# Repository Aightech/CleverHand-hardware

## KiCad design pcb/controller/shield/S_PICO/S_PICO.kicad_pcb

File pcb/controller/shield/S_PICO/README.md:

# pico shield
This shield is made to connect a pico board from seeed studio to the CleverHand bus and control the hmi modules.

## Electrical Schematic

## PCB Layout
|top view|side view|
|---|---|
|  |  |

## 3D Model
[S_PICO_3D](plots/S_PICO_pcb.stl)

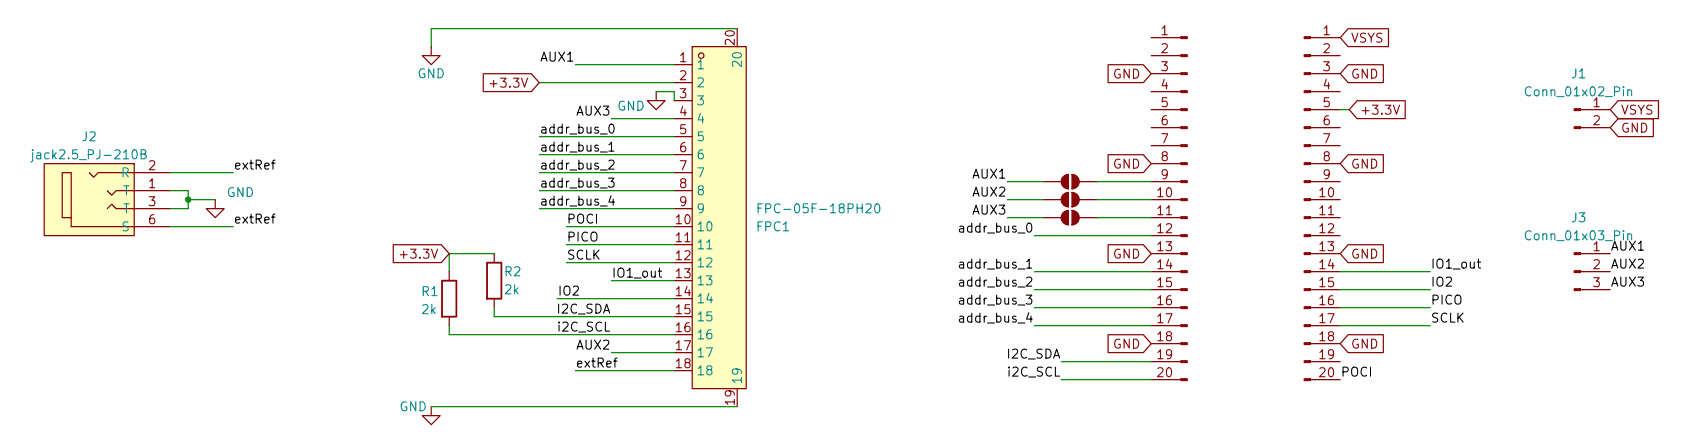
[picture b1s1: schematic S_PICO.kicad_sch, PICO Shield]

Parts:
FPC1: FPC-05F-18PH20; FPC-SMD_18P-P0.50_X05C2018TZ; LCSC Part C397324
J1: Conn_01x02_Pin; PinHeader_1x02_P1.27mm_Vertical
J2: jack2.5_PJ-210B; Jack_Socket_PJ-210B
J3: Conn_01x03_Pin; PinSocket_1x03_P1.27mm_Vertical
J4, J5: Conn_01x20_Male; PinHeader_1x20_P2.54mm_Vertical
JP2, JP3, JP4: SolderJumper_2_Open; SolderJumper-2_P1.3mm_Open_TrianglePad1.0x1.5mm
R1, R2: 2k; R_0402_1005Metric_Pad0.72x0.64mm_HandSolder; LCSC Part C4109

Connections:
+3.3V: FPC1.2, J5.5, R1.1, R2.1
/AUX1: FPC1.1, J3.1, JP2.1 (A)
/AUX2: FPC1.17, J3.2, JP3.1 (A)
/AUX3: FPC1.4, J3.3, JP4.1 (A)
/I2C_SDA: FPC1.15, J4.19, R2.2
/IO1_out: FPC1.13, J5.14
/IO2: FPC1.14, J5.15
/PICO: FPC1.11, J5.16
/POCI: FPC1.10, J5.20
/SCLK: FPC1.12, J5.17
/addr_bus_0: FPC1.5, J4.12
/addr_bus_1: FPC1.6, J4.14
/addr_bus_2: FPC1.7, J4.15
/addr_bus_3: FPC1.8, J4.16
/addr_bus_4: FPC1.9, J4.17
/extRef: FPC1.18, J2.2 (R), J2.6 (S)
/i2C_SCL: FPC1.16, J4.20, R1.2
GND: FPC1.3, FPC1.19, FPC1.20, J1.2, J2.1 (T), J2.3 (T), J4.3, J4.8, J4.13, J4.18, J5.3, J5.8, J5.13, J5.18
unnamed: J4.9, JP2.2 (B)
unnamed: J4.10, JP3.2 (B)
unnamed: J4.11, JP4.2 (B)
VSYS: J1.1, J5.1

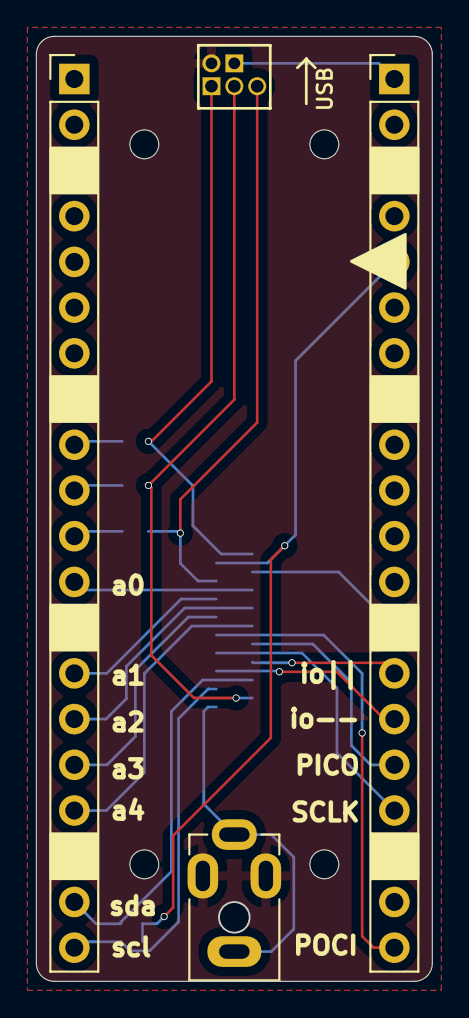
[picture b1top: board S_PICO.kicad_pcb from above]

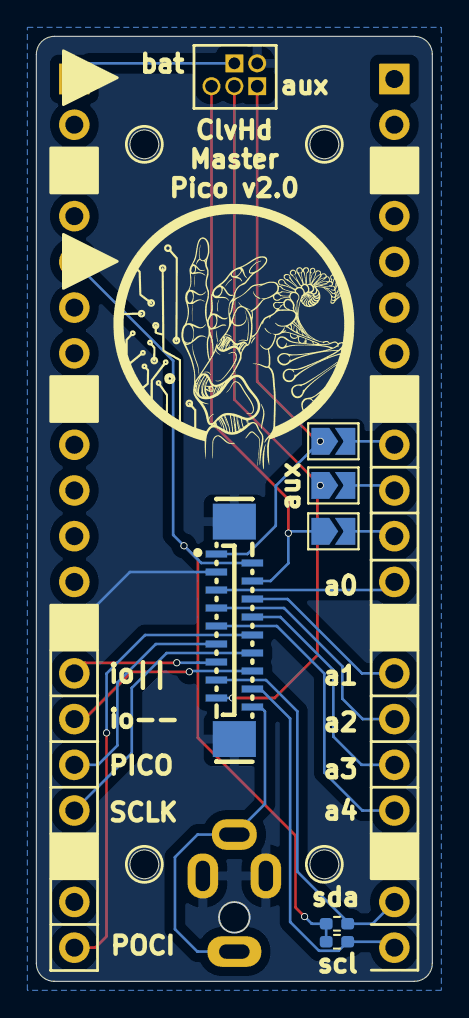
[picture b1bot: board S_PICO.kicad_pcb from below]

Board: 4 copper layers, 22.0 x 52.5 mm, 11 parts (6 on the bottom side), 22 nets.

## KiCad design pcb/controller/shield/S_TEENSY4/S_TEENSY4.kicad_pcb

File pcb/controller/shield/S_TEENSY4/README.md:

# XIAO shield
This shield is made to connect a teensy 4 board to the CleverHand bus and control the hmi modules.

## Electrical Schematic

## PCB Layout
|top view|side view|
|---|---|
|  |  |

## 3D Model
[S_TEENSY4_3D](plots/S_TEENSY4_pcb.stl)

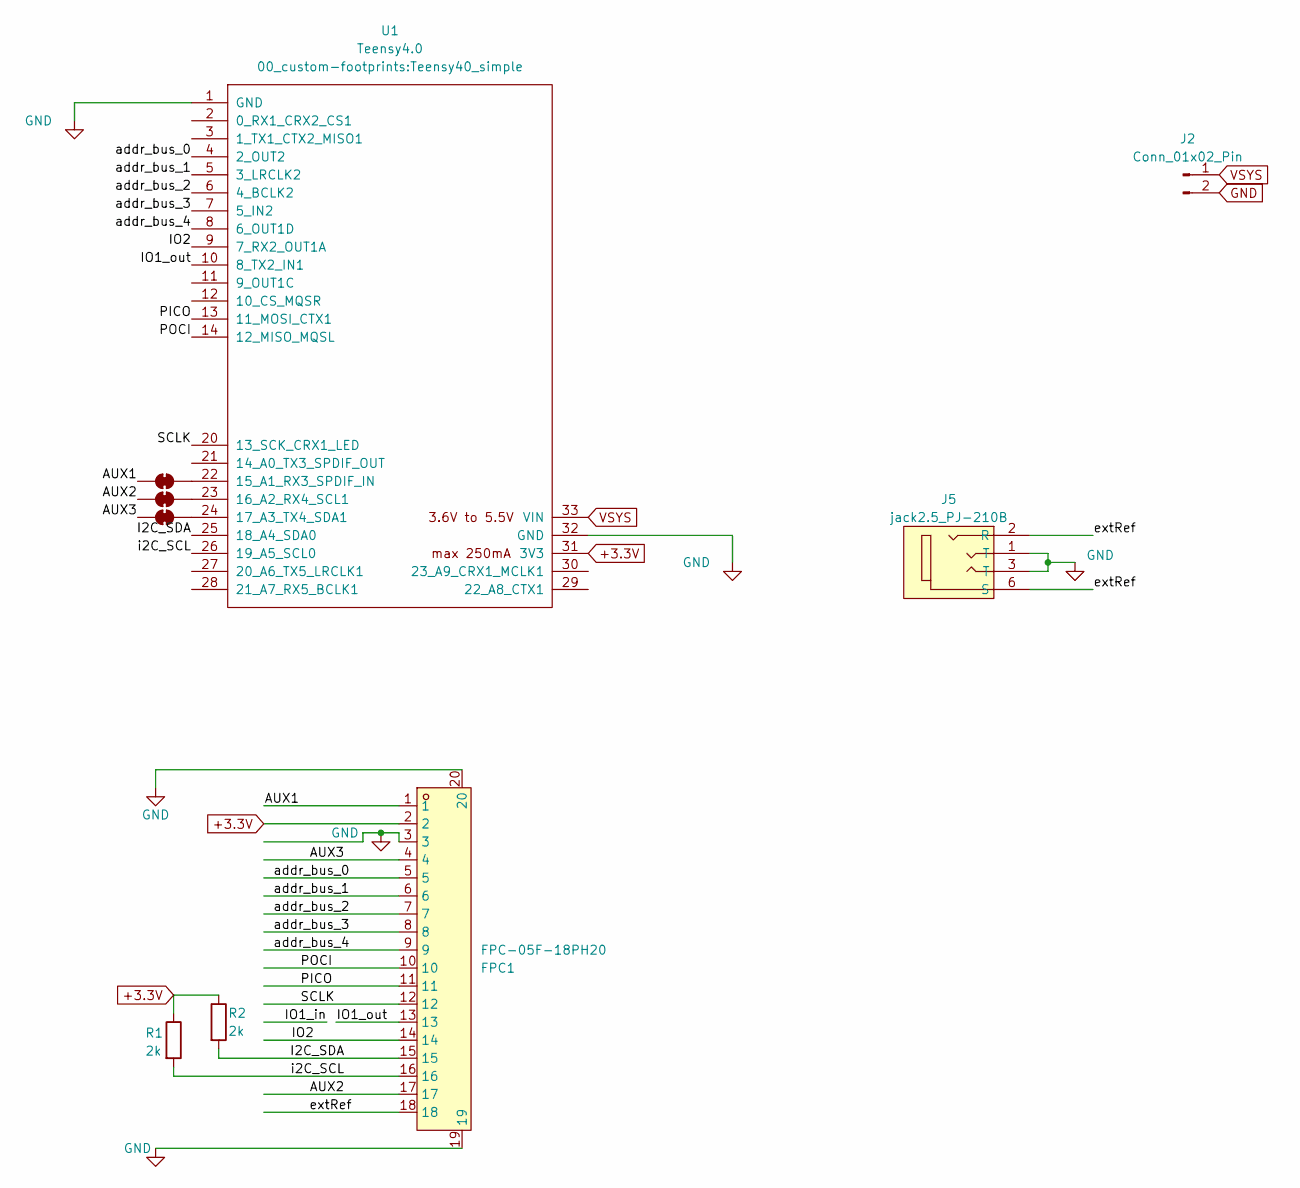
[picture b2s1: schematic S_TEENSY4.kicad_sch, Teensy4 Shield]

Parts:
FPC1: FPC-05F-18PH20; FPC-SMD_18P-P0.50_X05C2018TZ; LCSC Part C397324
J2: Conn_01x02_Pin; PinHeader_1x02_P1.27mm_Vertical
J5: jack2.5_PJ-210B; Jack_Socket_PJ-210B
JP1, JP2, JP3: SolderJumper_2_Bridged; SolderJumper-2_P1.3mm_Bridged_RoundedPad1.0x1.5mm
R1, R2: 2k; R_0402_1005Metric_Pad0.72x0.64mm_HandSolder; LCSC Part C4109
U1: Teensy4.0; Teensy40_simple

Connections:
+3.3V: FPC1.2, R1.1, R2.1, U1.31 (3V3)
/AUX1: FPC1.1, JP1.1 (A)
/AUX2: FPC1.17, JP2.1 (A)
/AUX3: FPC1.4, JP3.1 (A)
/I2C_SDA: FPC1.15, R2.2, U1.25 (18_A4_SDA0)
/IO1_out: FPC1.13, U1.10 (8_TX2_IN1)
/IO2: FPC1.14, U1.9 (7_RX2_OUT1A)
/PICO: FPC1.11, U1.13 (11_MOSI_CTX1)
/POCI: FPC1.10, U1.14 (12_MISO_MQSL)
/SCLK: FPC1.12, U1.20 (13_SCK_CRX1_LED)
/addr_bus_0: FPC1.5, U1.4 (2_OUT2)
/addr_bus_1: FPC1.6, U1.5 (3_LRCLK2)
/addr_bus_2: FPC1.7, U1.6 (4_BCLK2)
/addr_bus_3: FPC1.8, U1.7 (5_IN2)
/addr_bus_4: FPC1.9, U1.8 (6_OUT1D)
/extRef: FPC1.18, J5.2 (R), J5.6 (S)
/i2C_SCL: FPC1.16, R1.2, U1.26 (19_A5_SCL0)
GND: FPC1.3, FPC1.19, FPC1.20, J2.2, J5.1 (T), J5.3 (T), U1.1 (GND), U1.32 (GND)
unnamed: JP1.2 (B), U1.22 (15_A1_RX3_SPDIF_IN)
unnamed: JP2.2 (B), U1.23 (16_A2_RX4_SCL1)
unnamed: JP3.2 (B), U1.24 (17_A3_TX4_SDA1)
VSYS: J2.1, U1.33 (VIN)

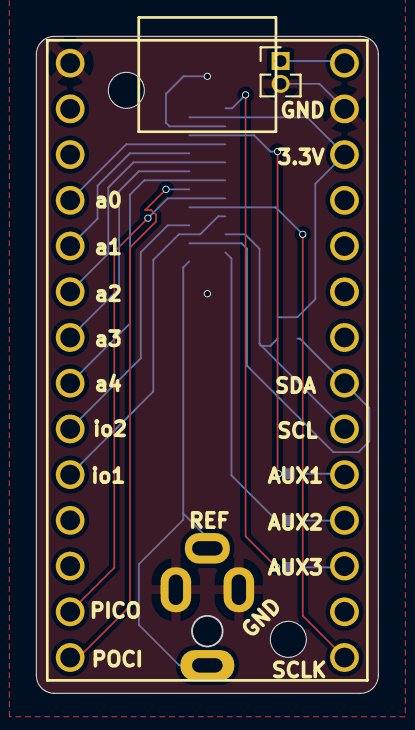
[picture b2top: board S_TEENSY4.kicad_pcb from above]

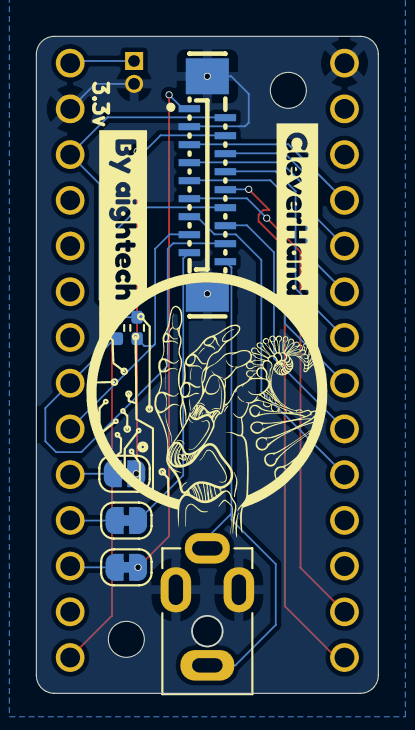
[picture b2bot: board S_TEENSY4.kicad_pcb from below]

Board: 4 copper layers, 19.0 x 36.5 mm, 11 parts (9 on the bottom side), 22 nets.

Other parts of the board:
kibuzzard-6611AB09: G***; kibuzzard-6611AB09
kibuzzard-6611ABB8: G***; kibuzzard-6611ABB8

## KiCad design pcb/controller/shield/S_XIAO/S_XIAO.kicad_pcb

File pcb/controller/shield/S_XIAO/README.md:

# XIAO shield
This shield is made to connect a XIAO board from seeed studio to the CleverHand bus and control the hmi modules.

## Electrical Schematic

## PCB Layout
|top view|side view|
|---|---|
|  |  |

## 3D Model
[S_XIAO_3D](plots/S_XIAO_pcb.stl)

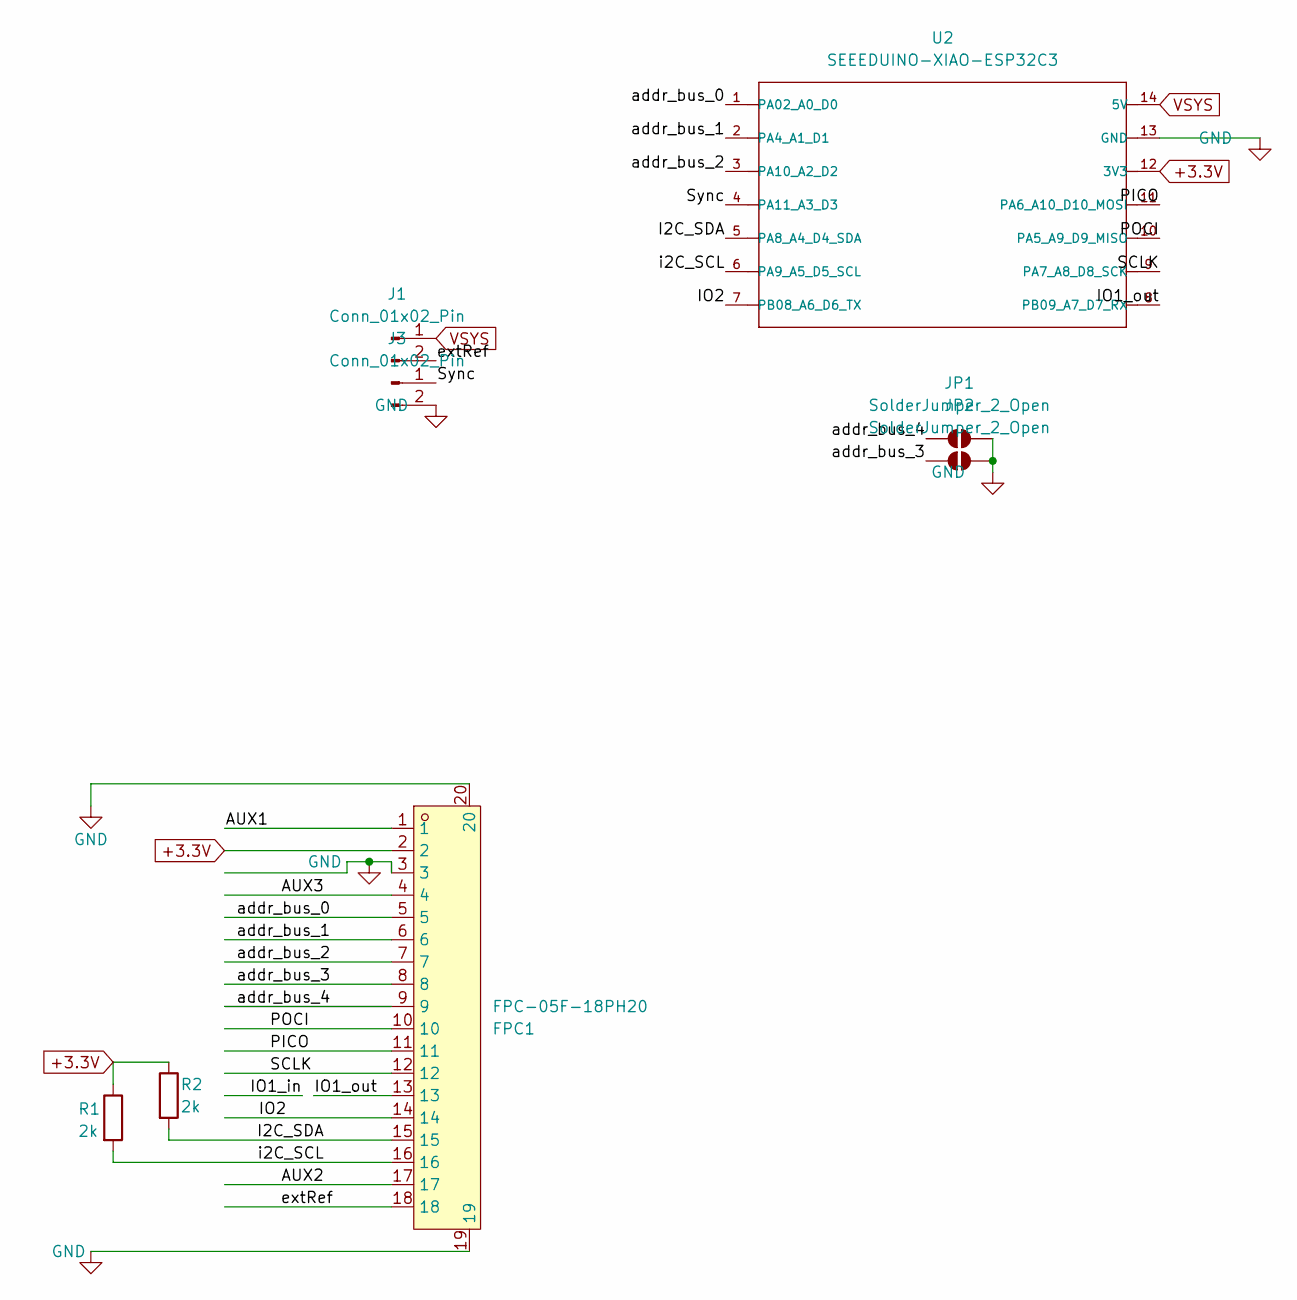
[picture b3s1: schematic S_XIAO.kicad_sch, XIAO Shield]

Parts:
FPC1: FPC-05F-18PH20; FPC-SMD_18P-P0.50_FPC-05F-18PH20; LCSC Part C397324
J1, J3: Conn_01x02_Pin; PinHeader_1x02_P2.54mm_Vertical
JP1, JP2: SolderJumper_2_Open; SolderJumper-2_P1.3mm_Open_Pad1.0x1.5mm
R1, R2: 2k; R_0402_1005Metric_Pad0.72x0.64mm_HandSolder; LCSC Part C4109
U2: SEEEDUINO-XIAO-ESP32C3; xiaoSeeedStudio_MODULE14P-DIP

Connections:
+3.3V: FPC1.2, R1.1, R2.1, U2.12 (3V3)
/AUX1: FPC1.1
/AUX2: FPC1.17
/AUX3: FPC1.4
/I2C_SDA: FPC1.15, R2.2, U2.5 (PA8_A4_D4_SDA)
/IO1_out: FPC1.13, U2.8 (PB09_A7_D7_RX)
/IO2: FPC1.14, U2.7 (PB08_A6_D6_TX)
/PICO: FPC1.11, U2.11 (PA6_A10_D10_MOSI)
/POCI: FPC1.10, U2.10 (PA5_A9_D9_MISO)
/SCLK: FPC1.12, U2.9 (PA7_A8_D8_SCK)
/Sync: J3.1, U2.4 (PA11_A3_D3)
/addr_bus_0: FPC1.5, U2.1 (PA02_A0_D0)
/addr_bus_1: FPC1.6, U2.2 (PA4_A1_D1)
/addr_bus_2: FPC1.7, U2.3 (PA10_A2_D2)
/addr_bus_3: FPC1.8, JP2.1 (A)
/addr_bus_4: FPC1.9, JP1.1 (A)
/extRef: FPC1.18, J1.2
/i2C_SCL: FPC1.16, R1.2, U2.6 (PA9_A5_D5_SCL)
GND: FPC1.3, FPC1.19, FPC1.20, J3.2, JP1.2 (B), JP2.2 (B), U2.13 (GND)
VSYS: J1.1, U2.14 (5V)

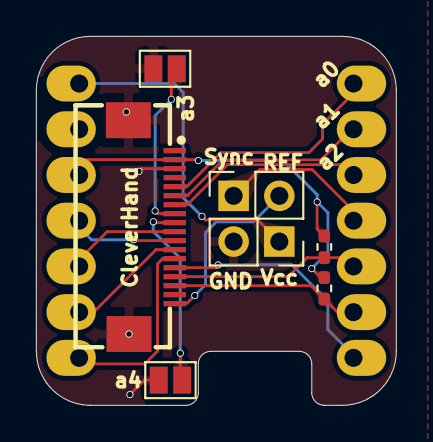
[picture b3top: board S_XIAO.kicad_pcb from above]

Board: 4 copper layers, 20.0 x 20.5 mm, 8 parts (1 on the bottom side), 17 nets.

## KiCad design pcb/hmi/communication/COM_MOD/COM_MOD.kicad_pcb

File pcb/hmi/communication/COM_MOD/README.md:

# Communication Module
This module is responsible for handling the communication between the different modules of the controller node.

The communication bus is composed of :
- Power supply (3.3V) and ground
- SPI bus (POCI, PICO, SCK)
- I2C bus (SDA, SCL)
- Address bus (A0, A1, A2, A3, A4)
- External reference voltage (AREF)

When the module is connected to the bus, it is assigned an address by the controller node. This address is used to identify the module on the bus.
The communication module will activate the chip select line of the associated sensor module when the address bus matches its address.
Additionally, each module has a unique identifier that is used to identify the module on the I2C bus.

## Electrical Schematic

## PCB Layout
|top view|side view|
|---|---|
 |  |  |

## 3D Model
[COM_MOD_3D](plots/COM_MOD_pcb.stl)

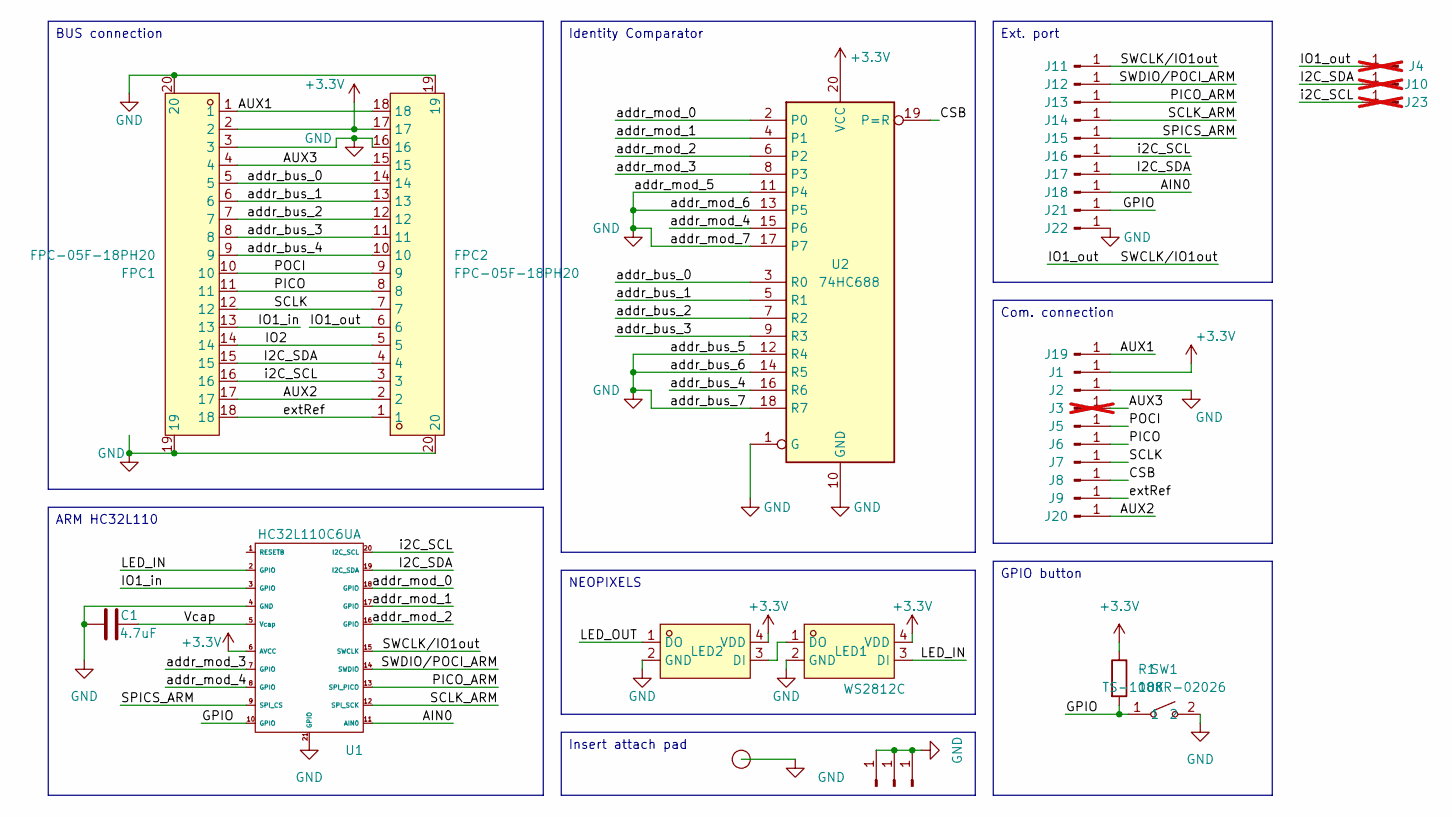
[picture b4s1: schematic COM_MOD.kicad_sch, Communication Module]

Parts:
C1: 4.7uF; C_0402_1005Metric; LCSC C23733
FPC1, FPC2: FPC-05F-18PH20; FPC-SMD_18P-P0.50_FPC-05F-18PH20; LCSC Part C2856802
I1: smd_insert; insert_1.2mm
J1, J2, J5, J6, J7, J8, J9, J11, J12, J13, J14, J15, J16, J17, J18, J19, J20, J21, J22: Conn_01x01_Pin; PinHeader_1x01_P1.27mm_Vertical
J3, J4, J10, J23: Conn_01x01_Pin; PinHeader_1x01_P1.27mm_Vertical; not fitted
J24, J25, J26: Conn_01x01_Pin; PinSocket_1x01_P2.54mm_Vertical
LED1, LED2: WS2812C; LED-SMD_4P-L2.0-W2.0-TL_WS2812B-2020; LCSC Part C2976072
R1: 10K; R_0402_1005Metric; LCSC C25744
SW1: TS-1088R-02026; SW-SMD_L3.9-W3.0-P4.45; LCSC Part C455280
U1: HC32L110C6UA; QFN-20-1EP_3x3mm_P0.4mm_EP1.4x1.4mm; LCSC C493490
U2: 74HC688; TSSOP-20_W4.4mm; LCSC C132045

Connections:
+3.3V: FPC1.2, FPC2.17, J1.1, LED1.4 (VDD), LED2.4 (VDD), R1.1, U1.6 (AVCC), U2.20 (VCC)
/AIN0: J18.1, U1.11 (AIN0)
/AUX1: FPC1.1, FPC2.18, J19.1
/AUX2: FPC1.17, FPC2.2, J20.1
/AUX3: FPC1.4, FPC2.15, J3.1
/CSB: J8.1, U2.19 (P=R)
/GPIO: J21.1, R1.2, SW1.1, U1.10 (GPIO)
/I2C_SDA: FPC1.15, FPC2.4, J10.1, J17.1, U1.19 (I2C_SDA)
/IO1_in: FPC1.13, U1.3 (GPIO)
/IO1_out: FPC2.6, J4.1, J11.1, U1.15 (SWCLK)
/IO2: FPC1.14, FPC2.5
/LED_IN: LED1.3 (DI), U1.2 (GPIO)
/LED_OUT: LED2.1 (DO)
/PICO: FPC1.11, FPC2.8, J6.1
/PICO_ARM: J13.1, U1.13 (SPI_PICO)
/POCI: FPC1.10, FPC2.9, J5.1
/SCLK: FPC1.12, FPC2.7, J7.1
/SCLK_ARM: J14.1, U1.12 (SPI_SCK)
/SPICS_ARM: J15.1, U1.9 (SPI_CS)
/SWDIO/POCI_ARM: J12.1, U1.14 (SWDIO)
/Vcap: C1.2, U1.5 (Vcap)
/addr_bus_0: FPC1.5, FPC2.14, U2.3 (R0)
/addr_bus_1: FPC1.6, FPC2.13, U2.5 (R1)
/addr_bus_2: FPC1.7, FPC2.12, U2.7 (R2)
/addr_bus_3: FPC1.8, FPC2.11, U2.9 (R3)
/addr_bus_4: FPC1.9, FPC2.10, U2.16 (R6)
/addr_mod_0: U1.18 (GPIO), U2.2 (P0)
/addr_mod_1: U1.17 (GPIO), U2.4 (P1)
/addr_mod_2: U1.16 (GPIO), U2.6 (P2)
/addr_mod_3: U1.7 (GPIO), U2.8 (P3)
/addr_mod_4: U1.8 (GPIO), U2.15 (P6)
/extRef: FPC1.18, FPC2.1, J9.1
/i2C_SCL: FPC1.16, FPC2.3, J16.1, J23.1, U1.20 (I2C_SCL)
GND: C1.1, FPC1.3, FPC1.19, FPC1.20, FPC2.16, FPC2.19, FPC2.20, I1.1 (conn), J2.1, J22.1, J24.1, J25.1, J26.1, LED1.2 (GND), LED2.2 (GND), SW1.2, U1.4 (GND), U1.21 (GPIO), U2.1 (G), U2.10 (GND), U2.11 (P4), U2.12 (R4), U2.13 (P5), U2.14 (R5), U2.17 (P7), U2.18 (R7)
unnamed: LED1.1 (DO), LED2.3 (DI)

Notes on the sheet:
ARM HC32L110
Insert attach pad
NEOPIXELS
Identity Comparator
Com. connection
GPIO button
BUS connection
Ext. port

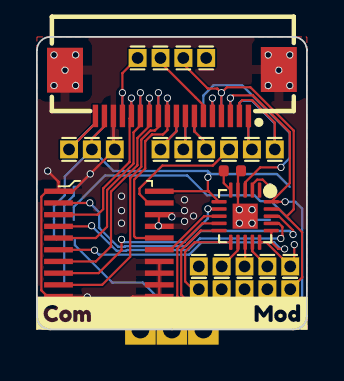
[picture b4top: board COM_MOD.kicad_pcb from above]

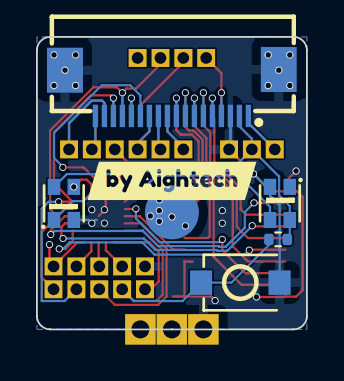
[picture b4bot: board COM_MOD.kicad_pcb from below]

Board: 4 copper layers, 15.0 x 16.3 mm, 38 parts (7 on the bottom side), 34 nets.

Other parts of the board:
kibuzzard-658C3FF8: G***; kibuzzard-658C3FF8
kibuzzard-658C2757: G***; kibuzzard-658C2757

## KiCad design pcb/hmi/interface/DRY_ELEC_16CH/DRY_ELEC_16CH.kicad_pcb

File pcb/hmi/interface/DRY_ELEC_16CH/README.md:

# Dry Electrodes Module
This module is responsible for interfacing the sensors/actuators inputs/outputs with the user skin or with other modules.

## Electrical Schematic

## PCB Layout
|top view|side view|
|---|---|
|||

## 3D Model
[DRY_ELEC_16CH_3D](plots/DRY_ELEC_16CH_pcb.stl)

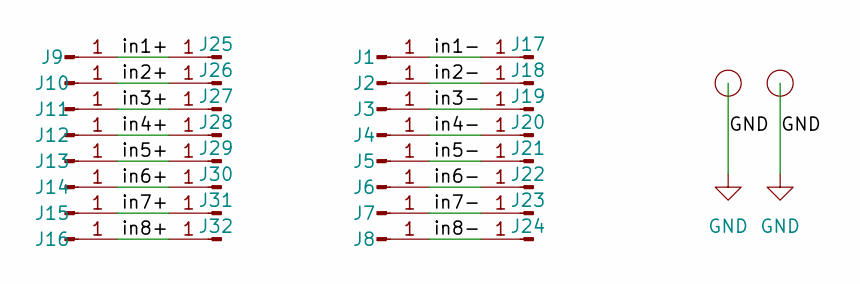
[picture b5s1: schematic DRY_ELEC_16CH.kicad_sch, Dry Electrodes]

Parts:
I3, I4: smd_insert; insert_1.2mm
J1, J2, J3, J4, J5, J6, J7, J8, J9, J10, J11, J12, J13, J14, J15, J16: Conn_01x01_Pin; SolderWirePad_1x01_SMD_1x2mm
J17, J18, J19, J20, J21, J22, J23, J24, J25, J26, J27, J28, J29, J30, J31, J32: Conn_01x01_Pin; Pin_D1.2mm_pogo

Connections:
/in1+: J9.1, J25.1
/in1-: J1.1, J17.1
/in2+: J10.1, J26.1
/in2-: J2.1, J18.1
/in3+: J11.1, J27.1
/in3-: J3.1, J19.1
/in4+: J12.1, J28.1
/in4-: J4.1, J20.1
/in5+: J13.1, J29.1
/in5-: J5.1, J21.1
/in6+: J14.1, J30.1
/in6-: J6.1, J22.1
/in7+: J15.1, J31.1
/in7-: J7.1, J23.1
/in8+: J16.1, J32.1
/in8-: J8.1, J24.1
GND: I3.1 (conn), I4.1 (conn)

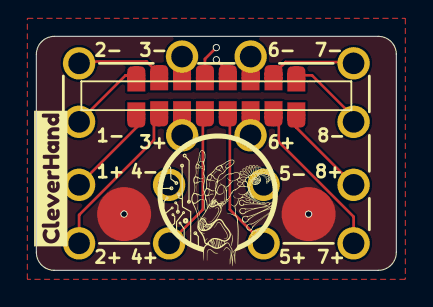
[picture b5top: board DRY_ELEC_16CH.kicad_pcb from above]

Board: 4 copper layers, 20.0 x 13.0 mm, 35 parts (0 on the bottom side), 17 nets.

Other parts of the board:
kibuzzard-660706DE: G***; kibuzzard-660706DE

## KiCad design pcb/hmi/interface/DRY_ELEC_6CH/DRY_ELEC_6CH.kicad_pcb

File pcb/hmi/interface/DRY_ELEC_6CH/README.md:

# Dry Electrodes Module
This module is responsible for interfacing the sensors/actuators inputs/outputs with the user skin or with other modules.

## Electrical Schematic

## PCB Layout
|top view|side view|
|---|---|
|||

## 3D Model
[DRY_ELEC_6CH_3D](plots/DRY_ELEC_6CH_pcb.stl)

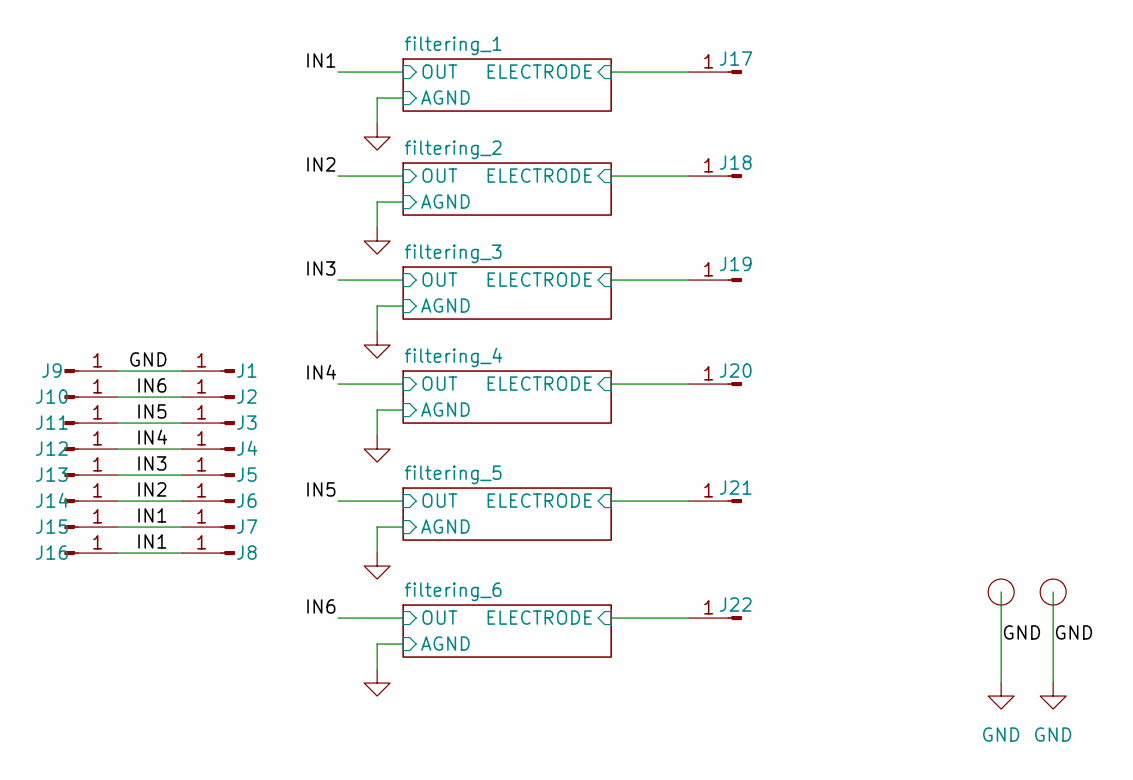
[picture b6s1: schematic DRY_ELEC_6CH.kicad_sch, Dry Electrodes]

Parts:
I3, I4: smd_insert; insert_1.2mm
J1, J2, J3, J4, J5, J6, J7, J8, J9, J10, J11, J12, J13, J14, J15, J16: Conn_01x01_Pin; SolderWirePad_1x01_SMD_1x2mm
J17, J18, J19, J20, J21, J22: Conn_01x01_Pin; Pin_D1.2mm_pogo

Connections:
/IN1: J7.1, J8.1, J15.1, J16.1; also elsewhere on the board
/IN2: J6.1, J14.1; also elsewhere on the board
/IN3: J5.1, J13.1; also elsewhere on the board
/IN4: J4.1, J12.1; also elsewhere on the board
/IN5: J3.1, J11.1; also elsewhere on the board
/IN6: J2.1, J10.1; also elsewhere on the board
/filtering_1/ELECTRODE: J17.1; also elsewhere on the board
/filtering_2/ELECTRODE: J18.1; also elsewhere on the board
/filtering_3/ELECTRODE: J19.1; also elsewhere on the board
/filtering_4/ELECTRODE: J20.1; also elsewhere on the board
/filtering_5/ELECTRODE: J21.1; also elsewhere on the board
/filtering_6/ELECTRODE: J22.1; also elsewhere on the board
GND: I3.1 (conn), I4.1 (conn), J1.1, J9.1; also elsewhere on the board

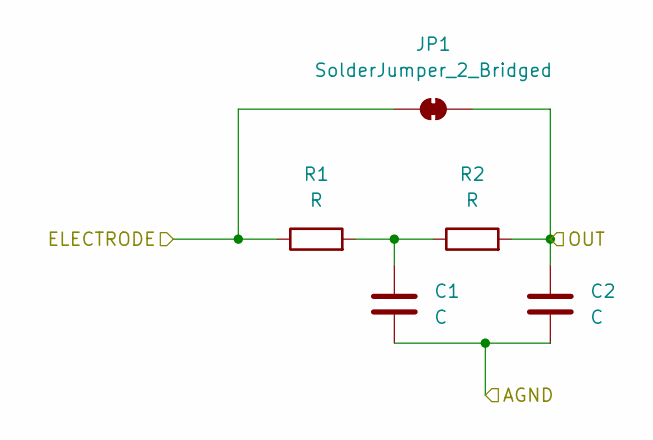
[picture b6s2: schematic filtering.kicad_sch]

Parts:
C1, C2: C; C_0402_1005Metric
JP1: SolderJumper_2_Bridged; SolderJumper-2_P1.3mm_Bridged_RoundedPad1.0x1.5mm
R1, R2: R; R_0402_1005Metric_Pad0.72x0.64mm_HandSolder

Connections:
/IN1: C2.1, JP1.2 (B), R2.2; also elsewhere on the board
/filtering_1/ELECTRODE: JP1.1 (A), R1.1; also elsewhere on the board
GND: C1.2, C2.2; also elsewhere on the board
unnamed: C1.1, R1.2, R2.1

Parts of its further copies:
C3, C4, C5, C6, C7, C8, C9, C10, C11, C12: C; C_0402_1005Metric
JP2, JP3, JP4, JP5, JP6: SolderJumper_2_Bridged; SolderJumper-2_P1.3mm_Bridged_RoundedPad1.0x1.5mm
R3, R4, R5, R6, R7, R8, R9, R10, R11, R12: R; R_0402_1005Metric_Pad0.72x0.64mm_HandSolder

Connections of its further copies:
/IN2: C4.1, JP2.2 (B), R4.2; also elsewhere on the board
/IN3: C6.1, JP3.2 (B), R6.2; also elsewhere on the board
/IN4: C8.1, JP4.2 (B), R8.2; also elsewhere on the board
/IN5: C10.1, JP5.2 (B), R10.2; also elsewhere on the board
/IN6: C12.1, JP6.2 (B), R12.2; also elsewhere on the board
/filtering_2/ELECTRODE: JP2.1 (A), R3.1; also elsewhere on the board
/filtering_3/ELECTRODE: JP3.1 (A), R5.1; also elsewhere on the board
/filtering_4/ELECTRODE: JP4.1 (A), R7.1; also elsewhere on the board
/filtering_5/ELECTRODE: JP5.1 (A), R9.1; also elsewhere on the board
/filtering_6/ELECTRODE: JP6.1 (A), R11.1; also elsewhere on the board
GND: C3.2, C4.2, C5.2, C6.2, C7.2, C8.2, C9.2, C10.2, C11.2, C12.2; also elsewhere on the board
unnamed: C3.1, R3.2, R4.1
unnamed: C5.1, R5.2, R6.1
unnamed: C7.1, R7.2, R8.1
unnamed: C9.1, R9.2, R10.1
unnamed: C11.1, R11.2, R12.1

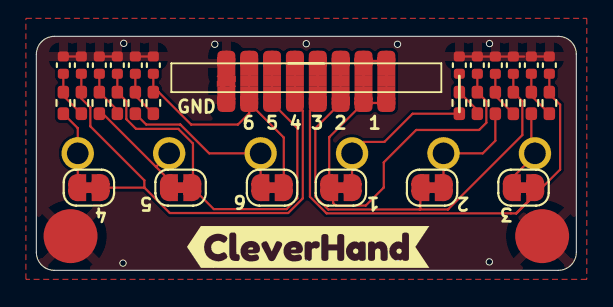
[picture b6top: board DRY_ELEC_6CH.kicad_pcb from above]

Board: 4 copper layers, 30.0 x 13.0 mm, 55 parts (0 on the bottom side), 19 nets.

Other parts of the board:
kibuzzard-66BA2E59: G***; kibuzzard-66BA2E59
